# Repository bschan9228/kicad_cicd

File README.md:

# About
CI/CD scripts for kicad to automatically export schematics, PCB drawings, gerbers, 3d model, etc.

## todo:
  - better naming semantics for files
  - makefile
  - remove unused hierarchial schematics/orphaned sheets - `./scripts/delete-unused-schematics.sh`

## interesting / useful repos
- https://github.com/labtroll/KiCad-DesignRules
- https://github.com/Bouni/kicad-jlcpcb-tools
- https://github.com/nguyen-v/KDT_Hierarchical_KiBot

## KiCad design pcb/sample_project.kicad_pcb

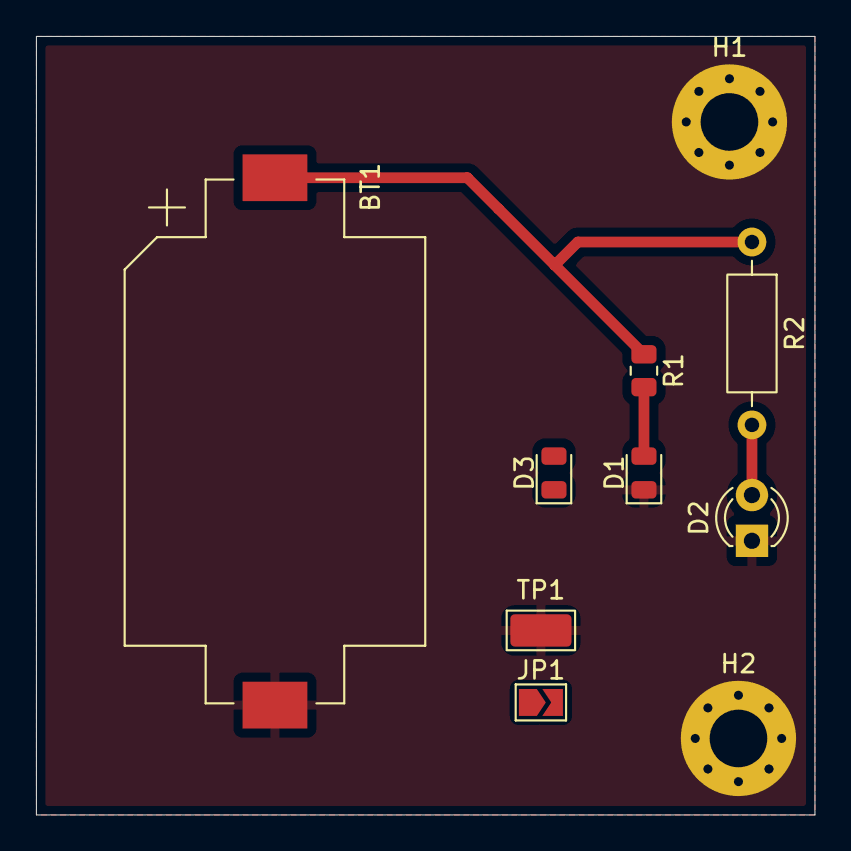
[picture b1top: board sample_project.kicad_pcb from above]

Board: 2 copper layers, 43.2 x 43.2 mm, 10 parts (0 on the bottom side), 4 nets.

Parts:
BT1: Battery_Cell; BatteryHolder_Keystone_1060_1x2032
D1, D3: LED_Small; LED_0805_2012Metric
D2: LED_Small; LED_D3.0mm
H1, H2: MountingHole_Pad; MountingHole_3.2mm_M3_Pad_Via
JP1: SolderJumper_2_Open; SolderJumper-2_P1.3mm_Open_TrianglePad1.0x1.5mm
R1: R_Small; R_0805_2012Metric
R2: R_Small; R_Axial_DIN0207_L6.3mm_D2.5mm_P10.16mm_Horizontal
TP1: TestPoint; TestPoint_Keystone_5015_Micro_Mini

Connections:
+BATT: BT1.1 (+), R1.1, R2.1
GND: BT1.2 (-), D1.1 (K), D2.1 (K), H1.1, TP1.1
unnamed: D1.2 (A), R1.2
unnamed: D2.2 (A), R2.2

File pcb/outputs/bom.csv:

"Reference","QUANTITY","Value","DNP","Part Number","URL","Footprint"
"BT1","1","Battery_Cell","","","","Battery:BatteryHolder_Keystone_1060_1x2032"
"D1,D3","2","LED_Small","","","","LED_SMD:LED_0805_2012Metric"
"D2","1","LED_Small","","","","LED_THT:LED_D3.0mm"
"R1","1","R_Small","DNP","","","Resistor_SMD:R_0805_2012Metric"
"R2","1","R_Small","","","","Resistor_THT:R_Axial_DIN0207_L6.3mm_D2.5mm_P10.16mm_Horizontal"
"TP1,TP2","2","TestPoint","","","","TestPoint:TestPoint_Keystone_5015_Micro_Mini"

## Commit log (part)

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2026-03-08 Added kicad export script
2026-03-08 Added schematic export workflow
2026-03-09 added docs
2026-03-09 updated gitignore
2026-03-10 small refactor
2026-03-12 added positions and 3D model
2026-03-12 fixed bom dnp's
2026-03-14 added some misc info
2026-03-14 added test points
2026-03-17 path relative to script
2026-03-28 changed filenames to underscores
2026-03-28 removed random file
2026-03-28 export path relative to project path
2026-03-28 changed dxf export to mm
2026-03-29 Fixed export path
2026-03-29 renamed some files and update comments
2026-04-02 regex for searching child schematics
2026-04-10 added drc & added quantity on export docs
